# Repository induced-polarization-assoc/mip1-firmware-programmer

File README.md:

# mip1-firmware-programmer
Hardware designs for an AVR-ICSP signal routing and tri-state buffer board for streamlining the firmware development workflow for MIP-1

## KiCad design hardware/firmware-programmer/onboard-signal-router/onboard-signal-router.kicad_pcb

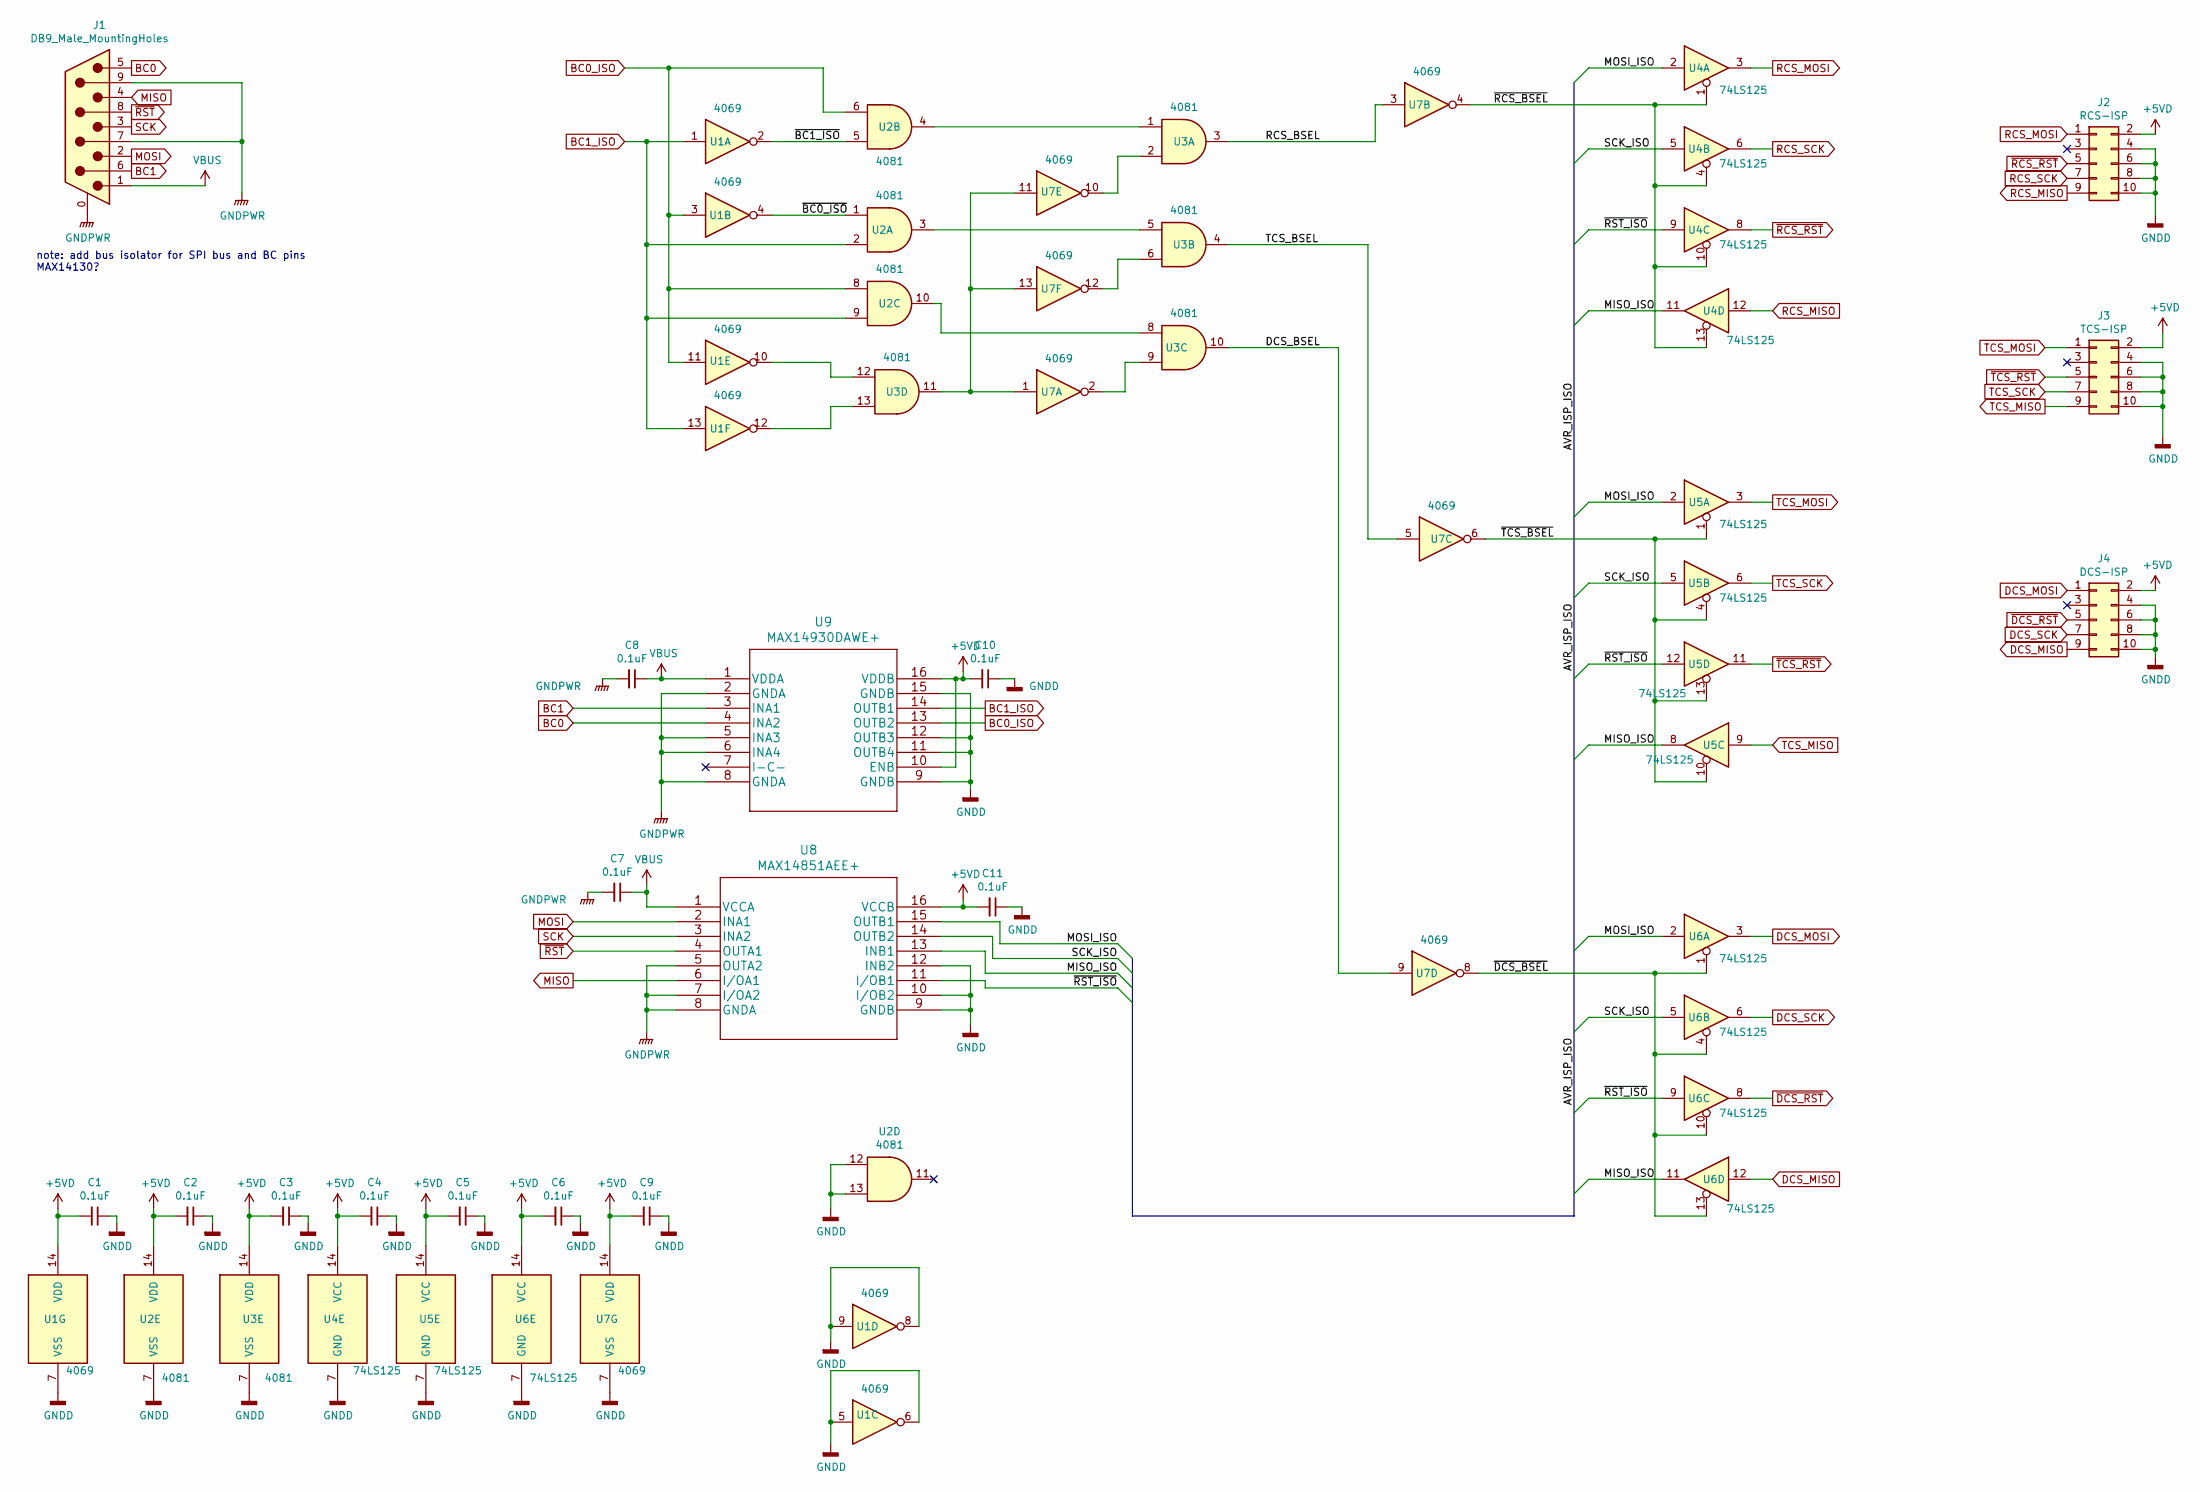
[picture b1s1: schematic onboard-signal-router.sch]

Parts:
C1, C2, C3, C4, C5, C6, C7, C8, C9, C10, C11: 0.1uF; C_0603_1608Metric_Pad1.05x0.95mm_HandSolder
J1: DB9_Male_MountingHoles; DSUB-9_Male_Vertical_P2.77x2.84mm_MountingHoles
J2: RCS-ISP; IDC-Header_2x05_P2.54mm_Vertical
J3: TCS-ISP; IDC-Header_2x05_P2.54mm_Vertical
J4: DCS-ISP; IDC-Header_2x05_P2.54mm_Vertical
U1, U7: 4069; SOIC-14_3.9x8.7mm_P1.27mm
U2, U3: 4081; SOIC-14_3.9x8.7mm_P1.27mm
U4, U5, U6: 74LS125; SOIC-14_3.9x8.7mm_P1.27mm
U8: MAX14851AEE+; MAX14851AEE&plus_
U9: MAX14930DAWE+; MAX14930DAWE&plus_

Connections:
+5VD: C1.2, C2.2, C3.2, C4.2, C5.2, C6.2, C9.2, C10.2, C11.2, J2.2, J3.2, J4.2, U1.14 (VDD), U2.14 (VDD), U3.14 (VDD), U4.14 (VCC), U5.14 (VCC), U6.14 (VCC), U7.14 (VDD), U8.16 (VCCB), U9.10 (ENB), U9.16 (VDDB)
/DCS_BSEL: U3.10, U7.9
/MISO_ISO: U4.11, U5.8, U6.11, U8.13 (INB1)
/MOSI_ISO: U4.2, U5.2, U6.2, U8.15 (OUTB1)
/RCS_BSEL: U3.3, U7.3
/SCK_ISO: U4.5, U5.5, U6.5, U8.14 (OUTB2)
/TCS_BSEL: U3.4, U7.5
/~BC0_ISO: U1.4, U2.1
/~BC1_ISO: U1.2, U2.5
/~DCS_BSEL: U6.1, U6.4, U6.10, U6.13, U7.8
/~RCS_BSEL: U4.1, U4.4, U4.10, U4.13, U7.4
/~RST_ISO: U4.9, U5.12, U6.9, U8.11 (I/OB1)
/~TCS_BSEL: U5.1, U5.4, U5.10, U5.13, U7.6
BC0: J1.5, U9.4 (INA2)
BC0_ISO: U1.3, U1.11, U2.6, U2.8, U9.13 (OUTB2)
BC1: J1.6, U9.3 (INA1)
BC1_ISO: U1.1, U1.13, U2.2, U2.9, U9.14 (OUTB1)
DCS_MISO: J4.9, U6.12
DCS_MOSI: J4.1, U6.3
DCS_SCK: J4.7, U6.6
GNDD: C1.1, C2.1, C3.1, C4.1, C5.1, C6.1, C9.1, C10.1, C11.1, J2.4, J2.6, J2.8, J2.10, J3.4, J3.6, J3.8, J3.10, J4.4, J4.6, J4.8, J4.10, U1.5, U1.6, U1.7 (VSS), U1.8, U1.9, U2.7 (VSS), U2.12, U2.13, U3.7 (VSS), U4.7 (GND), U5.7 (GND), U6.7 (GND), U7.7 (VSS), U8.9 (GNDB), U8.10 (I/OB2), U8.12 (INB2), U9.9 (GNDB), U9.11 (OUTB4), U9.12 (OUTB3), U9.15 (GNDB)
GNDPWR: C7.2, C8.2, J1.0 (PAD), J1.7, J1.9, U8.5 (OUTA2), U8.7 (I/OA2), U8.8 (GNDA), U9.2 (GNDA), U9.5 (INA3), U9.6 (INA4), U9.8 (GNDA)
MISO: J1.4, U8.6 (I/OA1)
MOSI: J1.2, U8.2 (INA1)
unnamed: U1.10, U3.12
unnamed: U1.12, U3.13
unnamed: U2.3, U3.5
unnamed: U2.4, U3.1
unnamed: U2.10, U3.8
unnamed: U3.2, U7.10
unnamed: U3.6, U7.12
unnamed: U3.9, U7.2
unnamed: U3.11, U7.1, U7.11, U7.13
RCS_MISO: J2.9, U4.12
RCS_MOSI: J2.1, U4.3
RCS_SCK: J2.7, U4.6
SCK: J1.3, U8.3 (INA2)
TCS_MISO: J3.9, U5.9
TCS_MOSI: J3.1, U5.3
TCS_SCK: J3.7, U5.6
VBUS: C7.1, C8.1, J1.1, U8.1 (VCCA), U9.1 (VDDA)
~DCS_RST: J4.5, U6.8
~RCS_RST: J2.5, U4.8
~RST: J1.8, U8.4 (OUTA1)
~TCS_RST: J3.5, U5.11

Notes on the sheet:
note: add bus isolator for SPI bus and BC pins MAX14130?

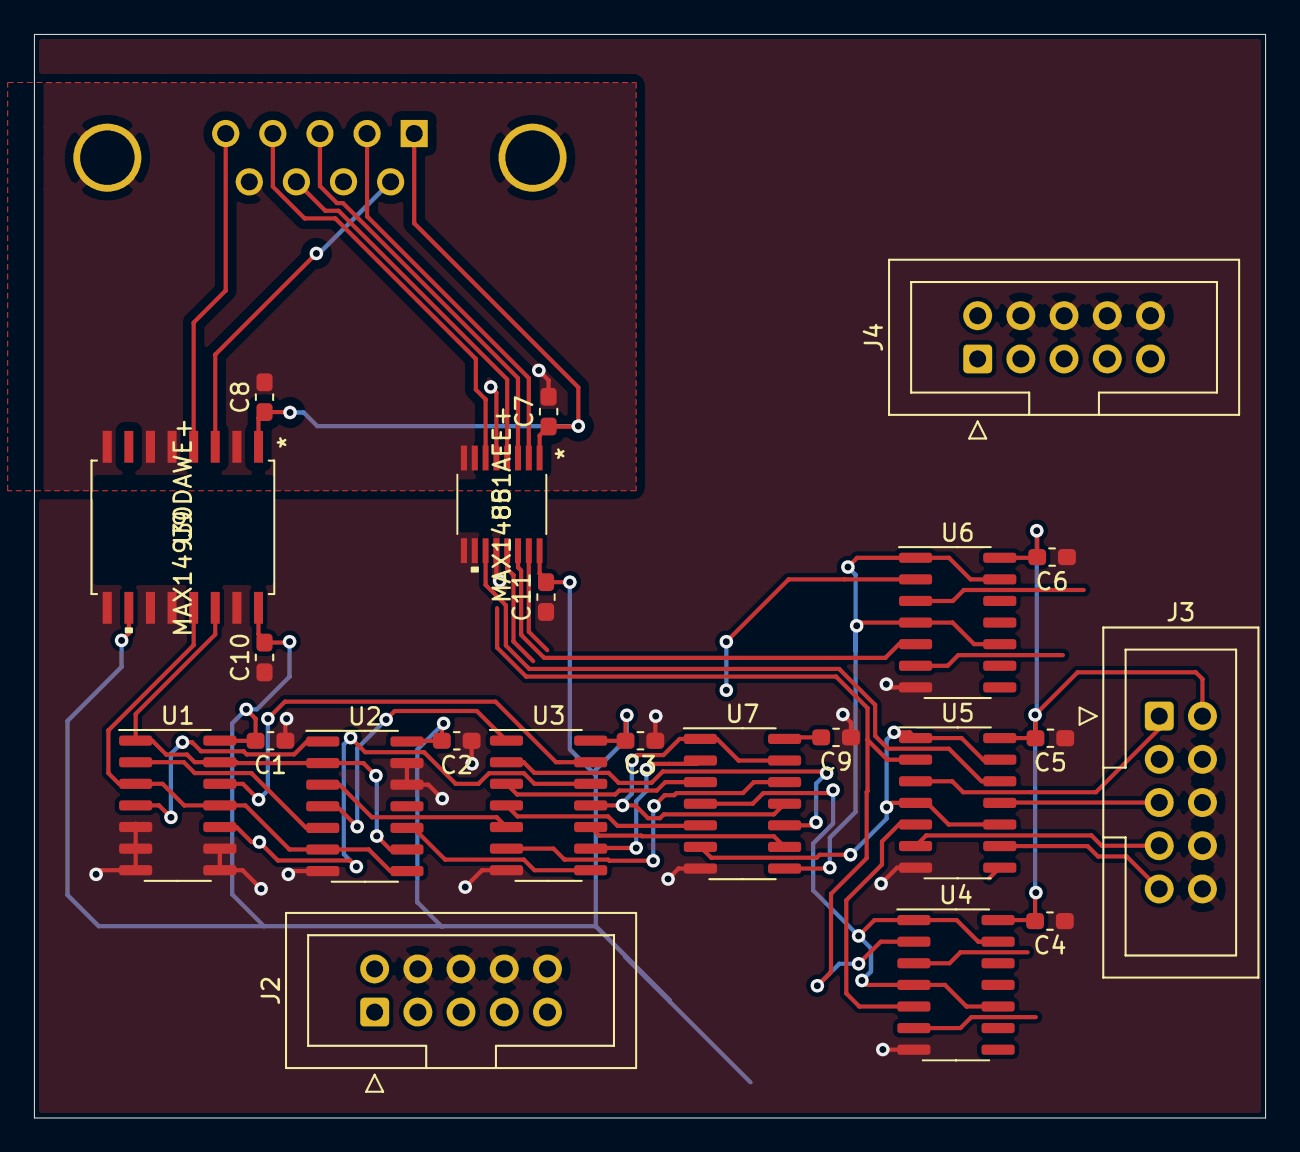
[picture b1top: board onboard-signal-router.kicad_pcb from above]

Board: 2 copper layers, 72.4 x 63.7 mm, 24 parts (1 on the bottom side), 45 nets.

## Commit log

2022-06-20 Created Logisim simulation of bus control logic for guiding the hardware layout.
2022-06-20 Added most of the necessary components for both the programming adapter and the onboard signal router. First local commit.
2022-07-19 mostly completed routing and board layout.

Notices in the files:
parts and their libraries:
Copyright 2021 Accelerated Designs. All rights reserved.
